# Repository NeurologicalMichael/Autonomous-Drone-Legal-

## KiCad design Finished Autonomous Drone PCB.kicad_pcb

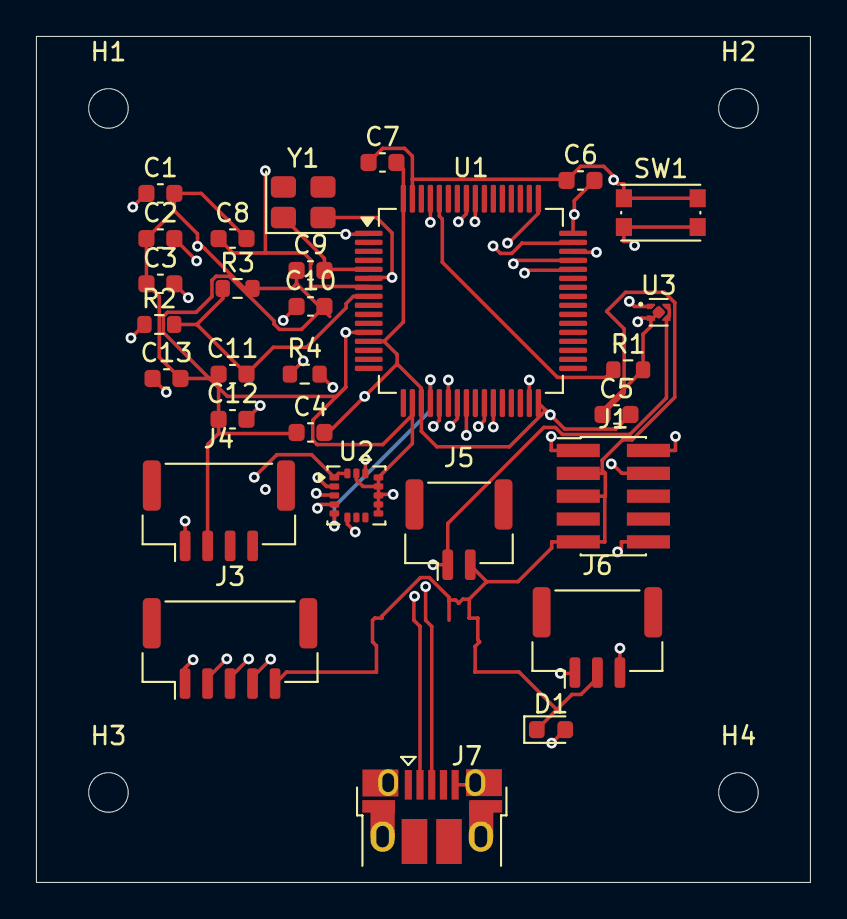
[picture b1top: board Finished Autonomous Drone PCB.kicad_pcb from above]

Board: 4 copper layers, 43.0 x 47.0 mm, 33 parts (0 on the bottom side), 28 nets.

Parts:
C1, C4, C5, C6, C7: 0.1uF; C_0603_1608Metric
C2, C3: 2.2; C_0603_1608Metric
C8: 0.1 µF; C_0603_1608Metric
C9, C10: 8.2; C_0603_1608Metric
C11: 100nF; C_0603_1608Metric
C12, C13: 1 µF; C_0603_1608Metric
D1: LED; LED_0603_1608Metric
H1, H2, H3, H4: MountingHole_2.2mm_M2
J1: Conn_ARM_JTAG_SWD_10; PinHeader_2x05_P1.27mm_Vertical_SMD
J3: Conn_01x05; JST_GH_BM05B-GHS-TBT_1x05-1MP_P1.25mm_Vertical
J4: Conn_01x04; JST_GH_BM04B-GHS-TBT_1x04-1MP_P1.25mm_Vertical
J5: Conn_01x02; JST_GH_BM02B-GHS-TBT_1x02-1MP_P1.25mm_Vertical
J6: Conn_01x03; JST_GH_BM03B-GHS-TBT_1x03-1MP_P1.25mm_Vertical
J7: USB_B_Micro; USB_Micro-B_Amphenol_10103594-0001LF_Horizontal
R1, R3: 10k; R_0603_1608Metric
R2: 47k; R_0603_1608Metric
R4: 1; R_0603_1608Metric
SW1: SW_Push; SW_Push_1P1T_NO_CK_KMR2
U1: STM32F405RGTx; LQFP-64_10x10mm_P0.5mm
U2: ICM-20602; LGA-16_3x3mm_P0.5mm_LayoutBorder3x5y
U3: TPS7A20xxxDQN; Texas_X2SON-4_1x1mm_P0.65mm
Y1: Crystal; Crystal_SMD_3225-4Pin_3.2x2.5mm

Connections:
+3.3V: C4.2, C5.2, C6.2, C7.2, C13.1, U1.13 (VDDA), U1.19 (VDD), U1.32 (VDD), U1.48 (VDD), U1.64 (VDD)
+3V3: J1.1 (VTref), J4.1, U1.1 (VBAT), U2.1 (VDDIO), U2.16 (VDD), U3.1 (OUT)
/5V_INPUT: C12.2, J5.1, J6.1, U3.3 (EN), U3.4 (IN)
/BAT_RAW: J6.3, R2.1
/NSRT: C8.1, J1.10 (~RESET), SW1.2, U1.7 (NRST)
/[MOTOR1]: J3.1, U1.56 (PB4)
/[MOTOR2]: J3.2, U1.57 (PB5)
/[MOTOR3]: J3.3, U1.26 (PB0)
/[MOTOR4]: J3.4, U1.27 (PB1)
/[VBAT_SENSE]: C11.2, R2.2, R3.1, U1.8 (PC0)
GND: C1.2, C2.1, C3.1, C4.1, C5.1, C6.1, C7.1, C8.2, C9.1, C10.2, C11.1, C12.1, C13.2, D1.1 (K), J1.3 (GND), J1.5 (GND), J1.9 (GNDDetect), J3.5, J4.2, J5.2, J6.2, J7.5 (GND), J7.SH (Shield), R1.2, R3.2, SW1.1, U1.12 (VSSA), U1.18 (VSS), U1.63 (VSS), U2.9 (GND), U2.10 (GND), U2.11 (GND), U2.12 (GND), U2.13 (GND), U2.15 (GND), U3.2 (GND), U3.5 (Pad)
unnamed: D1.2 (A), R4.2
unnamed: J1.4 (SWCLK/TCK), U1.49 (PA14)
unnamed: J1.2 (SWDIO/TMS), U1.46 (PA13)
unnamed: J7.3 (D+), U1.45 (PA12)
unnamed: J7.2 (D-), U1.44 (PA11)
unnamed: R1.1, U1.60 (BOOT0)
unnamed: U1.20 (PA4), U2.5 (~CS)
unnamed: U1.21 (PA5), U2.2 (SCL/SPC)
unnamed: U1.22 (PA6), U2.4 (SAO/SD0)
unnamed: U1.23 (PA7), U2.3 (SDA/SDI)
unnamed: R4.1, U1.61 (PB8)
unnamed: U1.24 (PC4), U2.6 (INT)
unnamed: C9.2, U1.5 (PH0), Y1.1
unnamed: C10.1, U1.6 (PH1), Y1.2
unnamed: C2.2, U1.31 (VCAP_1)
unnamed: C3.2, U1.47 (VCAP_2)
unnamed: C1.1, U2.14 (REGOUT)
